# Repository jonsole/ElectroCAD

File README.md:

# ElectroCAD

Schematic capture and 2/4-layer PCB layout that runs in the browser or as a desktop app, with the look and feel of DabbleCAD.

**Status:** early development. The app shell is in place (ticket #2); see the spec in issue #1 and `docs/DESIGN.md` for the plan.

```bash
npm install
npm run dev          # browser, http://localhost:5190
npm start            # desktop (Electron)
npm test             # unit tests (node --test)
npm run test:smoke   # end-to-end smoke journeys in real Electron (Linux: uses xvfb-run when there is no display)
```

- Domain glossary: `CONTEXT.md`
- Decisions: `docs/adr/`
- Architecture and milestones: `docs/DESIGN.md`
- Screen layout and DabbleCAD-style components: `docs/UI.md`

Licensed under Apache-2.0. Parts are ported from DabbleCAD; see `NOTICE`.

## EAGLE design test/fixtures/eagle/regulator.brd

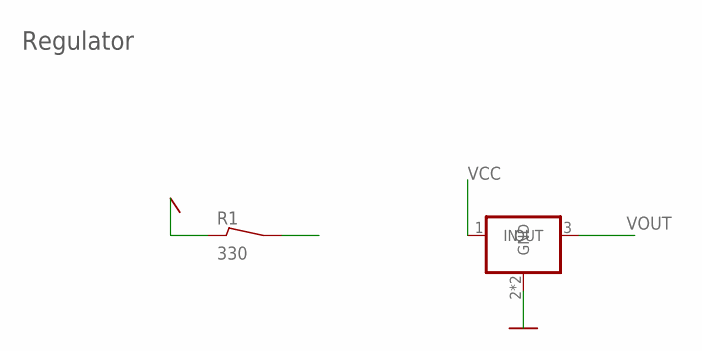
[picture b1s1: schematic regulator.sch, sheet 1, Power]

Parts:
R1: 330; R0805
U1: 78XX05SOT223; SOT223

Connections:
GND: U1.2 (GND), U1.4 (GND); also elsewhere on the board
VCC: R1.1, U1.1 (IN); also elsewhere on the board
VOUT: U1.3 (OUT); also elsewhere on the board

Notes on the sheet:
Regulator

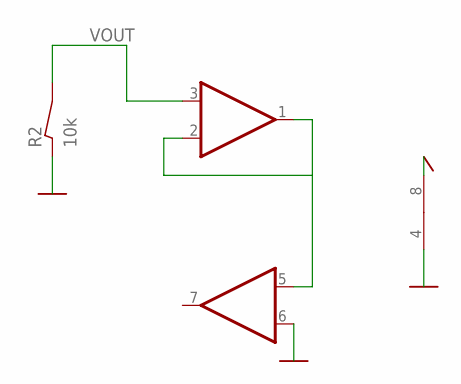
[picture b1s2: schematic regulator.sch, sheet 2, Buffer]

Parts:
R2: 10k; 0207/10
U2: LM358D; SO8

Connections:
AOUT: U2.1 (OUT), U2.2 (-IN), U2.5 (+IN)
GND: R2.1, U2.4 (V-), U2.6 (-IN); also elsewhere on the board
VCC: U2.8 (V+); also elsewhere on the board
VOUT: R2.2, U2.3 (+IN); also elsewhere on the board

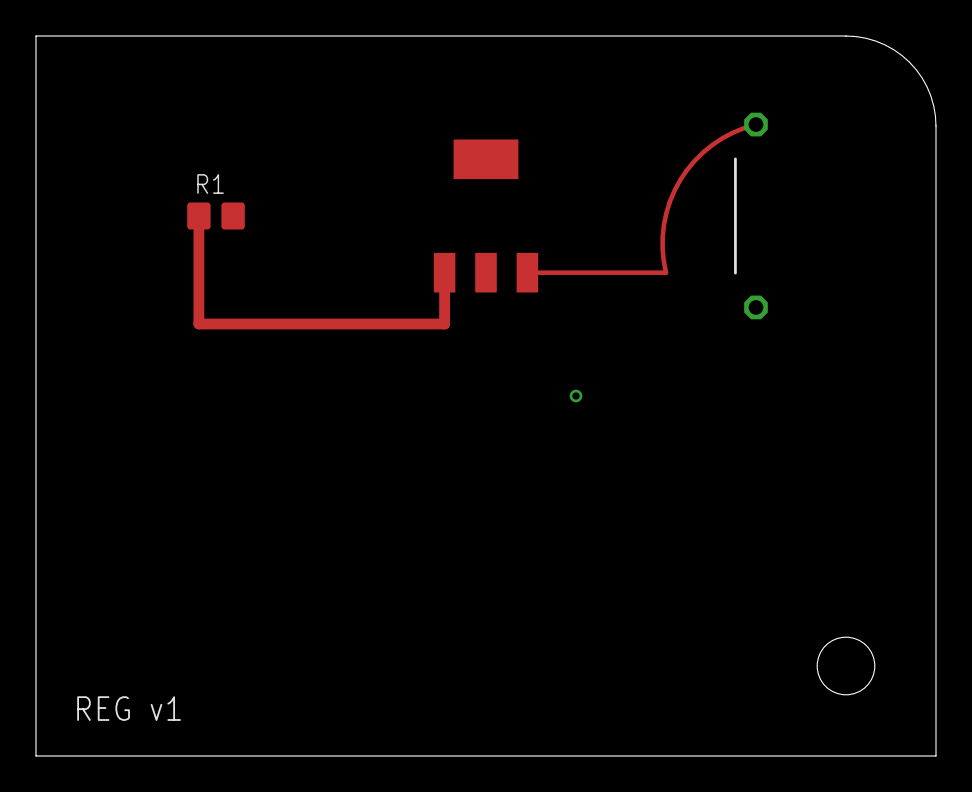
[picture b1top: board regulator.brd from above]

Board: 2 copper layers, 50.0 x 40.0 mm, 4 parts (1 on the bottom side), 4 nets.
